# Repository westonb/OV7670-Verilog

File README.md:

# OV7670-Verilog
Verilog modules required to get the OV7670 camera working on the Nexys4-DDR board for MIT's 6.111 Digital Systems Labratory

# Introduction
I highly recommend you first read the data sheet for the camera module: http://www.voti.nl/docs/OV7670.pdf
In summary OV7670 utilizes a 8 bit parallel bus to output video data along with HREF and VSYNC signals to synchronize frames. A input clock is required which is used as a reference for generating the output pixel output clock that the data is aligned to. 

# Configuration 
The OV7670 requires configuration to output the correct color format with the proper color balance. This is done over SCCB which is a copy of the I2C protocol. This interface is over the camera SIOC and SIOD pins. A configuration module is provided for you which will configure the camera with reasonable settings for RGB565 data output. 

# Camera Data Capture
A module is provided which interfaces with the 8 bit parallel and the HREF/VSYNC signals to output pixel data, a pixel valid signal, and a frame done signal. This can be interfaced with a frame buffer of your own creation. To fit on the Nexys4-DDR BRAM memory you will have to downsample the image in either terms of size or the size of the stored pixel. It is also possible, although complicated to full frames in the on board DDR memory.

# Hardware Configuration
The OV7670 outputs its own pixel clock (PCLOCK) that is synchronized with its data output. This must be connected to the FPGA and you must capture the data in this clock domain. Only some PMOD pins are capable of being used as a clock input. The PCLOCK pin must connect to (JB10) for the right PMOD connectors. If you have two cameras you should be able to get away with using one PCLOCK to capture the data from both as long as you connect the clock input from the cameras to the same source. Any of the other PMOD pins can be used for the other camera signals. The 3.3V supply for the camera can also be sourced from the PMOD connectors.

# SCCB Pullup Resistors
The SCCB interface for the camera requires pull up resistors. You need to solder 4.7K resistors from the SIOD and SIOC pins on the camera to the 3.3V supply. You can do this yourself or have the staff in the EDS help you.

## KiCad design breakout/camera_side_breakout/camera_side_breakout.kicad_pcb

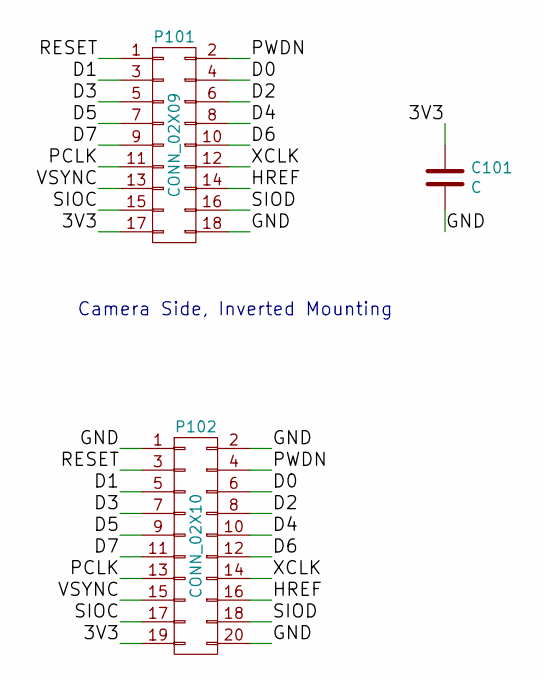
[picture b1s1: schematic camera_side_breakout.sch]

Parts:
C101: C; C_0805
P101: CONN_02X09; Pin_Header_Straight_2x09
P102: CONN_02X10; Pin_Header_Straight_2x10

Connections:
/3V3: C101.1, P101.17, P102.19
/D0: P101.4, P102.6
/D1: P101.3, P102.5
/D2: P101.6, P102.8
/D3: P101.5, P102.7
/D4: P101.8, P102.10
/D5: P101.7, P102.9
/D6: P101.10, P102.12
/D7: P101.9, P102.11
/GND: C101.2, P101.18, P102.1, P102.2, P102.20
/HREF: P101.14, P102.16
/PCLK: P101.11, P102.13
/PWDN: P101.2, P102.4
/RESET: P101.1, P102.3
/SIOC: P101.15, P102.17
/SIOD: P101.16, P102.18
/VSYNC: P101.13, P102.15
/XCLK: P101.12, P102.14

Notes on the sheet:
Camera Side, Inverted Mounting

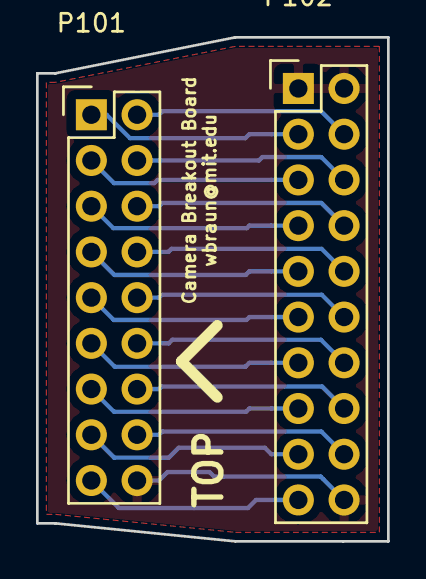
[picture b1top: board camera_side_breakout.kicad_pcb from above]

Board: 2 copper layers, 19.5 x 28.0 mm, 3 parts (1 on the bottom side), 18 nets.

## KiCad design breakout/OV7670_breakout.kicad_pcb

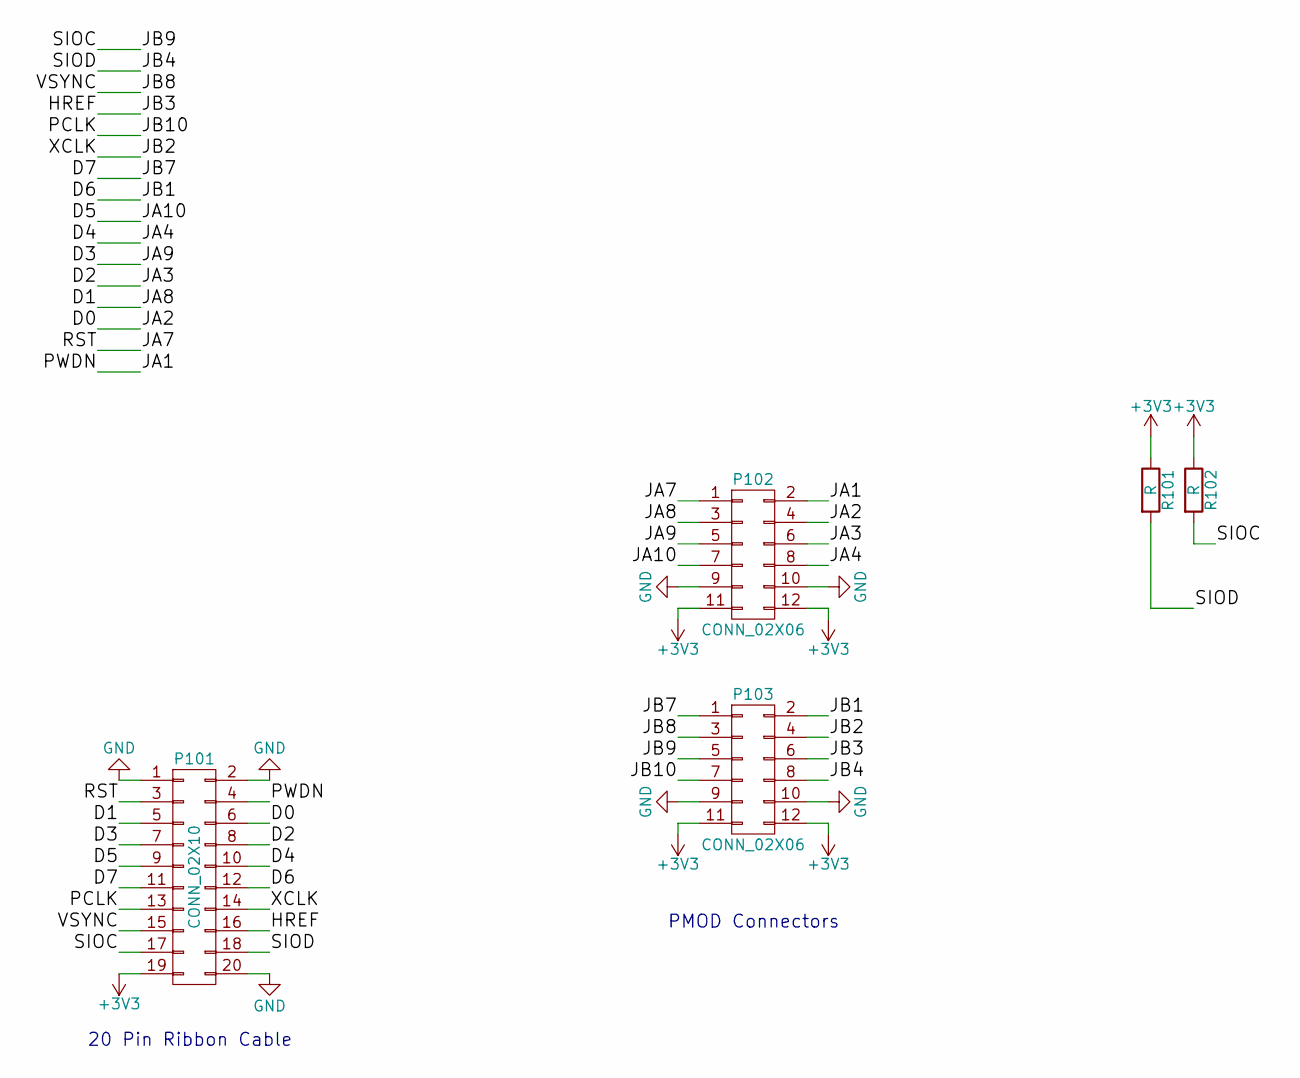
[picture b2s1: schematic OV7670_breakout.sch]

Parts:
P101: CONN_02X10; Pin_Header_Straight_2x10
P102, P103: CONN_02X06; Pin_Header_Straight_2x06
R101, R102: R; R_0805

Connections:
+3V3: P101.19, P102.11, P102.12, P103.11, P103.12, R101.1, R102.1
/D0: P101.6, P102.4
/D1: P101.5, P102.3
/D2: P101.8, P102.6
/D3: P101.7, P102.5
/D4: P101.10, P102.8
/D5: P101.9, P102.7
/D6: P101.12, P103.2
/D7: P101.11, P103.1
/HREF: P101.16, P103.6
/JA1: P101.4, P102.2
/JA7: P101.3, P102.1
/JB2: P101.14, P103.4
/JB4: P101.18, P103.8, R101.2
/JB8: P101.15, P103.3
/JB9: P101.17, P103.5, R102.2
/JB10: P101.13, P103.7
GND: P101.1, P101.2, P101.20, P102.9, P102.10, P103.9, P103.10

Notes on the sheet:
PMOD Connectors
20 Pin Ribbon Cable

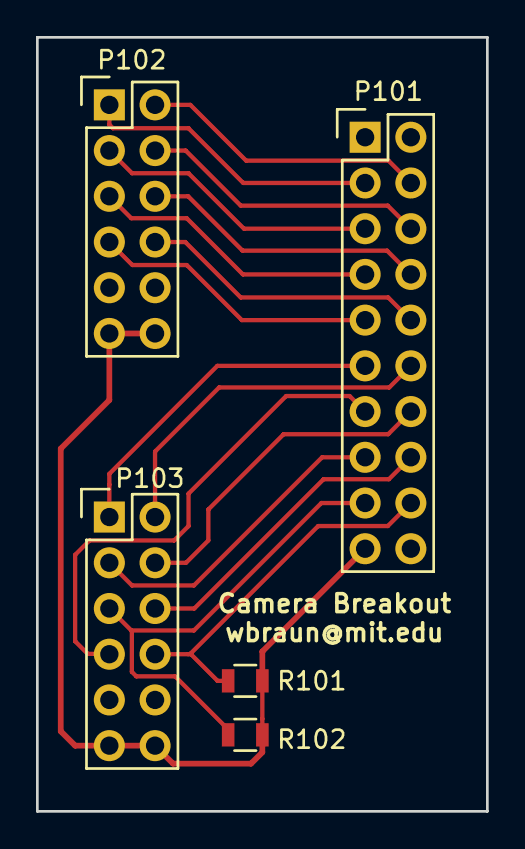
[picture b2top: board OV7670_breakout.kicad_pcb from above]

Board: 2 copper layers, 25.0 x 43.0 mm, 5 parts (0 on the bottom side), 18 nets.

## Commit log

2015-11-07 added scr and testbenches
2015-11-16 fixed clock capable input pin error
2016-11-01 updated config rom, made breakout board for camera
2018-07-26 new breakout board
2018-07-26 updated kicad files
